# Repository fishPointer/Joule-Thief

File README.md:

# Joule Thief

## Overview
- **Purpose:** Exhibition project at Open Sauce July 18-20, 2025, Practice
- **Description:** High efficiency alkaline battery draining system with diagnostics and energy storage
- **Domain:** Precision energy harvesting & instrumentation

**Objectives:**
- Extract all usable electrical energy from used/"dead" Alkaline Cells (AA, AAA, etc.)
- Measure & Log energy extraction data from each cell & deliver analytics
- Efficiently convert and push energy extracted into a Li-Ion power bank

**Topology**
- **INA219** - Energy Metering
- **LTC3105** - Low Voltage Boost Converter
- **AD5280** - Digital Potentiometer, 200kΩ
- **DW01** - 18650 Single-cell BMS
- **TP4056** - Single-cell 18650 Charger
- **FS8205** - Dual-FET package for DW01
- **AO3400** - Low Voltage N-E-FET
- **1N5817** - Low Voltage Schottky Diode

**Status:** Complete. Exhibited. Working on Finalizing Documentation.

**Additional Documentation:** available on my Obsidian at [suneaterlabs.com](https://suneaterlabs.com).

**Why Joule Thief?**
This project was started as a New Year's Resolution to exhibit at Open Sauce 2025, and was finished 2 days prior to the event.
I have no commercial intent with this project. I don't believe that it is particularly novel, and a close look by anyone experienced with energy harvesting & power electronics should rightly reveal it as something akin to a useless machine.

I teach myself new skills by designing projects that require to develop the skills I want in order to complete them. I put a high level of effort into this project because I wanted to go through the process of designing a relatively performant embedded system without referencing anyone else's work. Just pick functionalities and features, set a spec, and then flip through datasheets until you find the right combination. Then put it all together and prove that it works. Design the schematic, route a board, write the firmware, etc. and then package it all up and provide thorough documentation on the whole thing.

I had never done any of that before and I have no professional experience working as an electronics engineer. I do have an EE degree and currently work in power system analysis for hyperscale datacenters, so this project is actually something like a microcosm of my day job. There is little overlap though, and I consider myself self-taught here. I learned a lot!

## System Description

### Joule Thief - Core Functionality

The Joule Thief is designed to fully deplete alkaline cells of any remaining energy, long after they will fail to turn on their devices. The core of this design is the LTC3105, which can handle input voltages as low as 250mV. A quick look at an alkaline cell's SOC-OCV curve will show that draining to 300mV is sufficient to say >99% of total energy has been drained.

The classic Joule Thief is a simple party trick involving a dead battery, a hand-wound toroid, and a BJT. It is essentially using the voltage spike from inductive kickback to PWM an LED back to life. My motivation for this project was to demonstrate that there is a considerable amount of energy left in alkaline cells when they are discarded, so I set out to build an overengineered energy harvester that could precisely quantify how much energy was actually left in a dead cell, and then store it into a lithium-based battery bank to further prove the point.

 In order to improve performance and maximize both energy throughput and conversion efficiency, there is an INA219 shunt meter on either side of the LTC3105 boost chip allowing for efficiency tracking during processing & live diagnostics. 
 Additionally, the LTC3105 includes an MPPC pin, which enables a variable resistance to throttle the inductor's switching in order to achieve a specified input voltage. With the addition of an AD5280-200kΩ digital potentiometer attached to the MPPC pin, it is possible to read in energy measurements from the INA219's into a microcontroller, and then adjust the setting of the LTC3105 accordingly. The result is a control loop that can maximize the energy extraction rate regardless of the target cell's health or state of charge. 
 
 This INA219+LTC3105+AD5280 system can be tuned for maximum efficiency or maximum average power extracted, but optimizing for energy throughput has far greater performance gains. Using a DC Electronic Load to produce a slow sweep of load resistance values across a fresh AA alkaline cell will result in no more than 400-500mW peak extraction rate, and chemical effects such as electrolyte gradient formation and ion depletion make this power output unstable and liable to rapidly decline. The dynamic approach explored in the Joule Thief is able to achieve 900-1100mW peak output power, and can reliably maintain 600-700mW extraction rate in the early life of a cell. Additionally, the MPPC schema prevents the cell's output capacity from being overwhelmed by the battery chemistry effects, and the cell will continuously output higher power than traditional Joule Thief circuits or static loads.

The Joule Thief Extraction Module is also designed to run in "headless" mode without an MCU. No diagnostics are available in this mode (obviously) and the board will be able to move the energy from a single AA cell into a single 18650 cell safely.

### Joule Chief - Core Functionality

The Joule Chief was designed to be a mainboard that allows for the consolidation of harvested energy from an arbitrary number of Joule Thief Extraction Modules collecting energy from different sources at different rates. The Joule Chief serves as both an aggregator and an abstraction layer for the energy harvested. 

The Joule Chief begins with a low-voltage schottky diode on the output of the extraction module to prevent backflow. After the energy is delivered to the mainboard's input bus, all the energy is stored in a 1F supercapacitor. The Joule Thief Extraction Modules are all set to boost whatever energy source they are targeting to 5V and charge the 1F supercap to 5V accordingly. 

Readings from the mainboard's INA219 allow the MCU to precisely track the voltage of the supercap as well as the power flowing into this buffer. The MCU is programmed to operate a schmitt trigger with thresholds at 2.5V and 5V, only enabling the 1F supercap's energy to pass through the mainboard's LTC3105 after 5V has been reached, and until 2.5V. This region of input voltage allows the boost chip to operate in a high-efficiency mode.

Once the energy has moved through the 1F supercap and through the LTC3105, it is stored in a second 1F supercap connected to the lithium cell charger. The cell charger is controlled by a second schmitt trigger running on the MCU as well. This schmitt trigger keeps the second 1F energy buffer between 4.5V and 5.0V, such that the buffer will always be an appropriate voltage for charging a lithium cell (3.0V to 4.3V).

The Joule Chief can handle an arbitrary number of extraction modules each working on arbitrarily weak or intermittent energy sources. This mainboard can effectively accumulate these energy sources and efficiently deposit this energy via intermittent pulses of energy into a rechargeable battery bank for later use while providing precise diagnostics at every stage of the harvesting process. The frequency of these charging pulses is dependent on the strength of the sources. Harvesting a sufficiently powerful source, such as a fresh AA cell, will allow the mainboard to achieve steady-state operation, and a continuous current flow into the 18650 becomes possible.

Both the Joule Thief and Joule Chief boards currently use a generic and inefficient BMS stack consisting of a DW01 for OC/OCD/SC protection, an FS8205 dual-FET package for breaking the circuit, and a TP4056 charging IC. This BMS is largely unnecessary given the low-power nature of this application, but was included for safety and peace of mind.

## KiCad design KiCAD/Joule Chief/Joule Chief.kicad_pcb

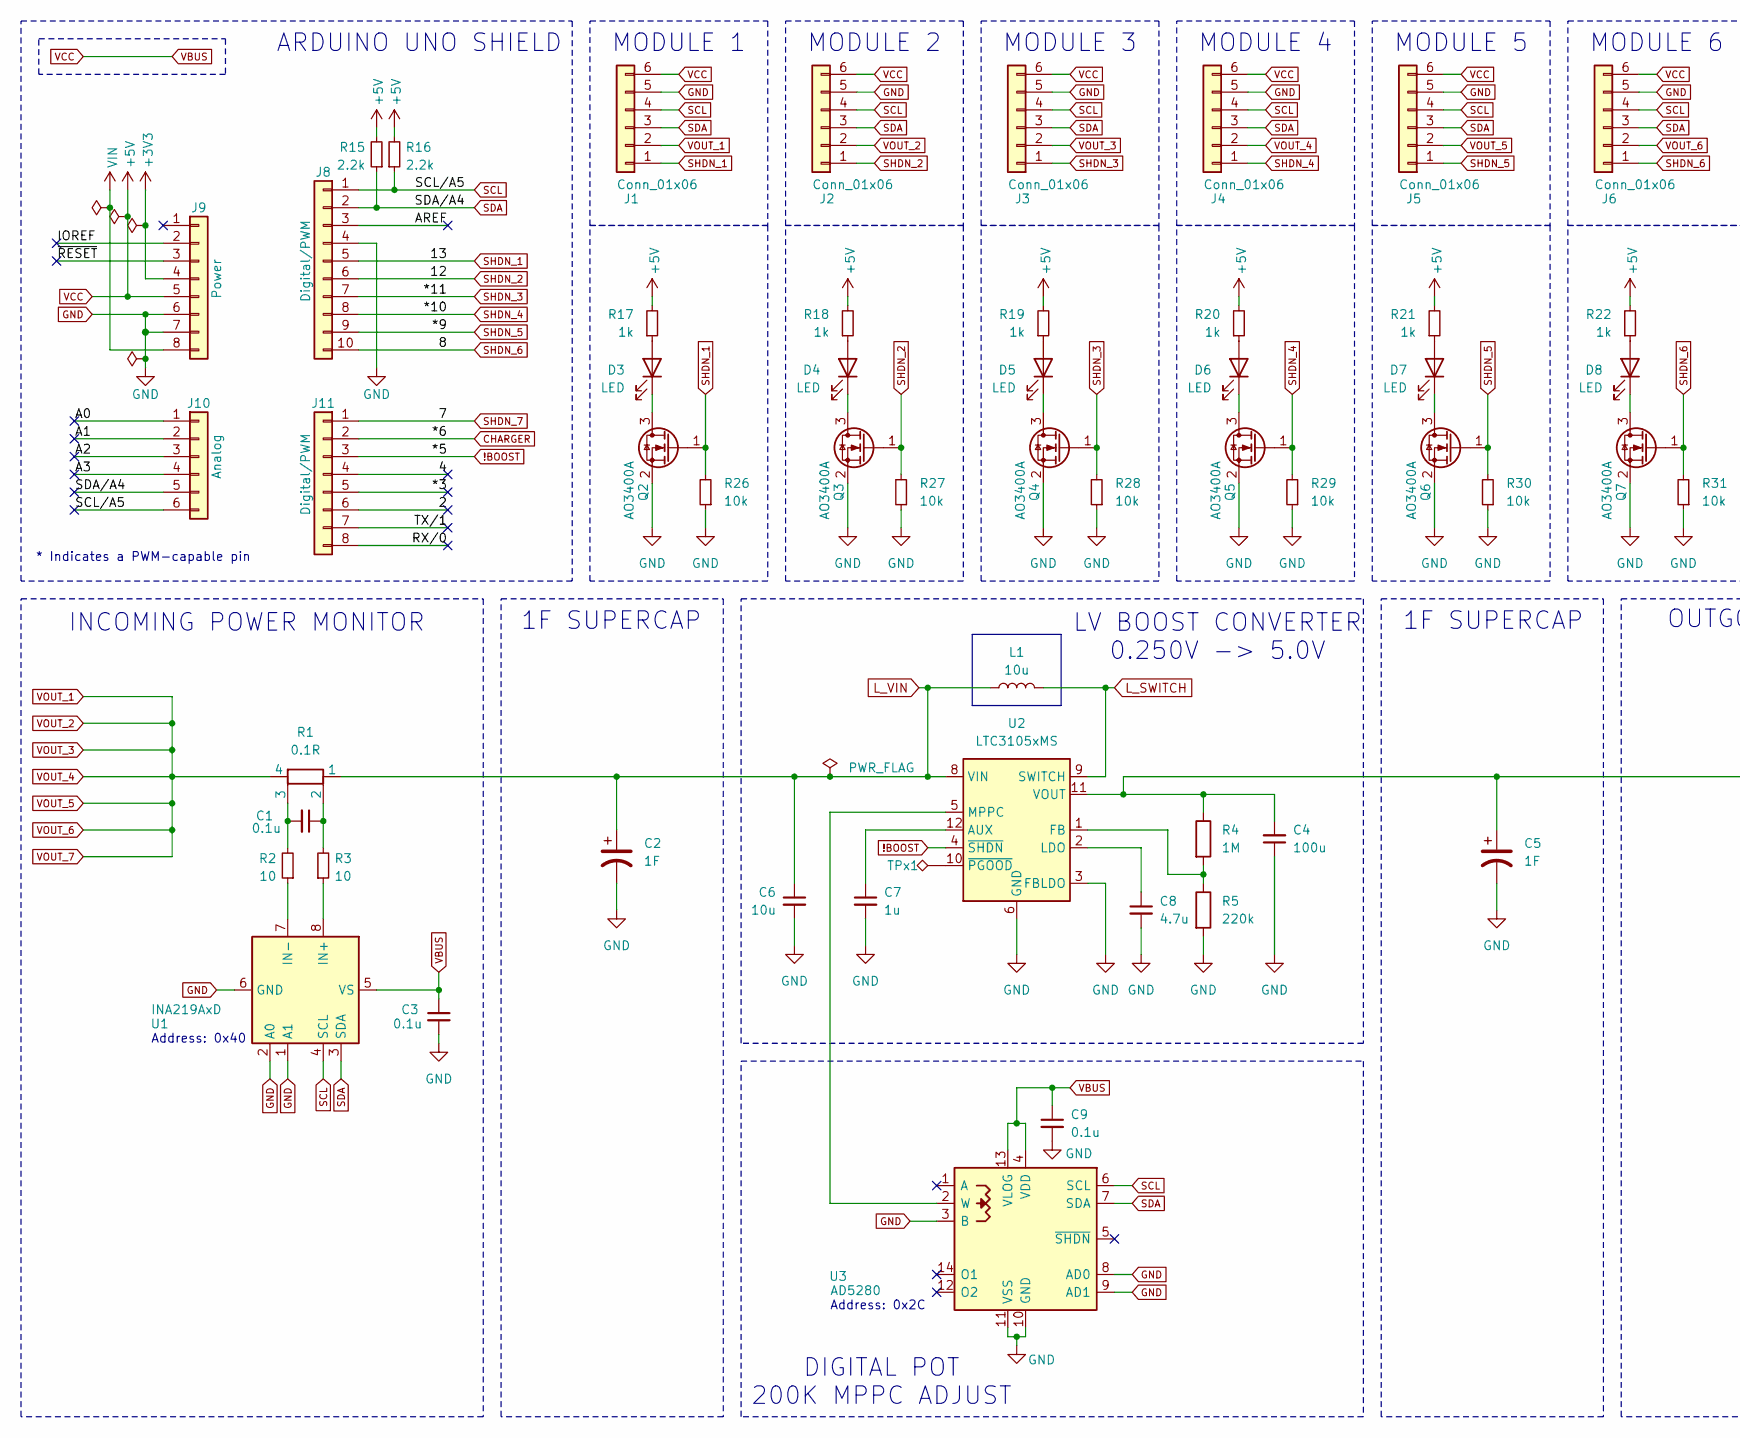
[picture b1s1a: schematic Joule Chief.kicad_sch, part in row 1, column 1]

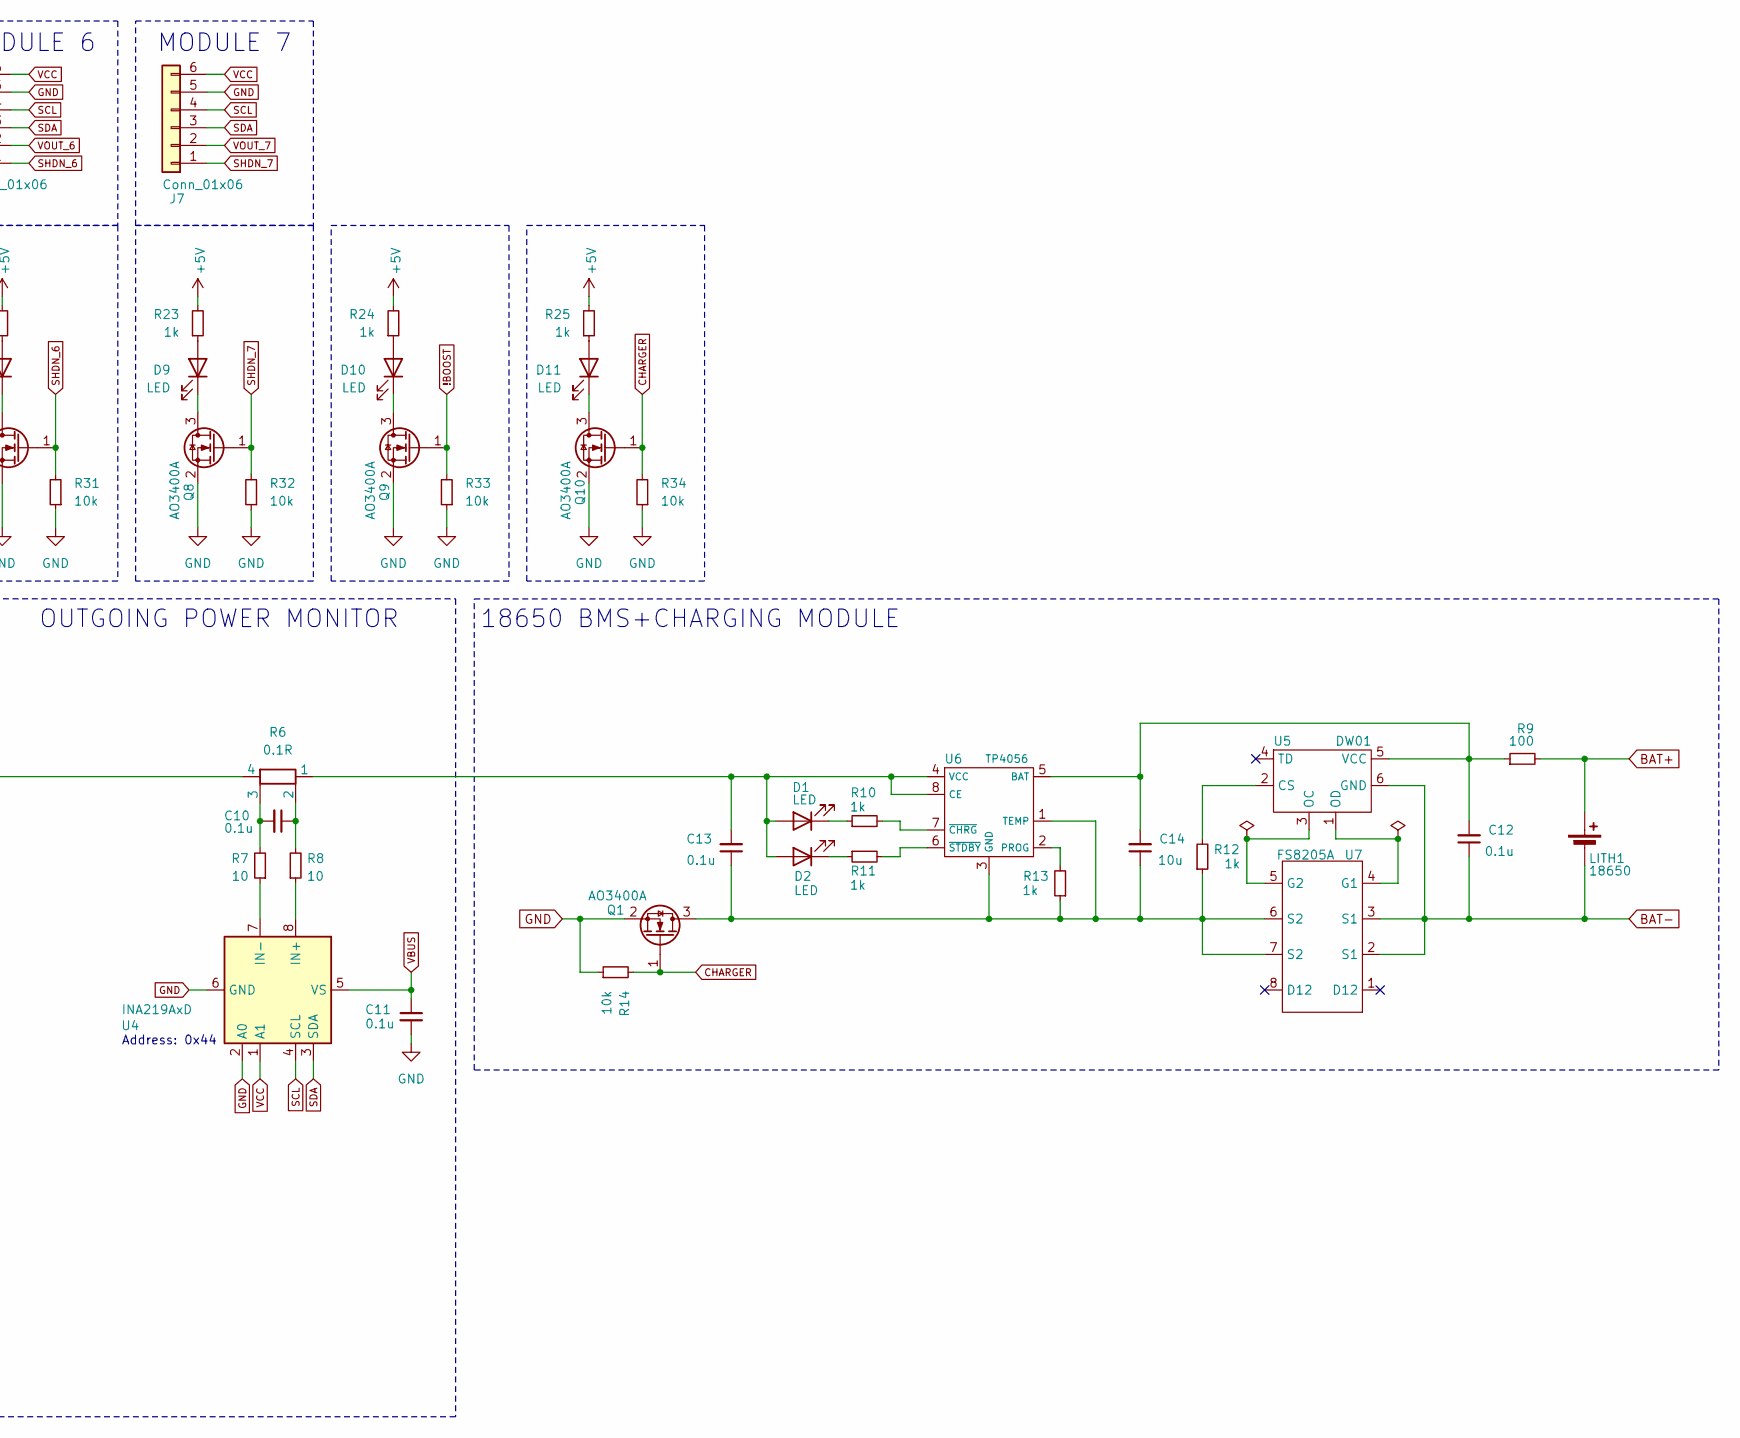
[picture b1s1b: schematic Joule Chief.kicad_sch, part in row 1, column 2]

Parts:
C1, C3, C9, C10, C11, C12, C13: 0.1u; C_0805_2012Metric_Pad1.18x1.45mm_HandSolder
C2, C5: 1F; 1F_Supercap
C4: 100u; CP_Radial_D5.0mm_P2.00mm
C6, C14: 10u; C_0805_2012Metric_Pad1.18x1.45mm_HandSolder
C7: 1u; C_0805_2012Metric_Pad1.18x1.45mm_HandSolder
C8: 4.7u; C_0805_2012Metric_Pad1.18x1.45mm_HandSolder
D1, D2, D3, D4, D5, D6, D7, D8, D9, D10, D11: LED; LED_0805_2012Metric_Pad1.15x1.40mm_HandSolder
J1, J2, J3, J4, J5, J6, J7: Conn_01x06; JST_PH_B6B-PH-K_1x06_P2.00mm_Vertical
J8: Digital/PWM; PinSocket_1x10_P2.54mm_Vertical
J9: Power; PinSocket_1x08_P2.54mm_Vertical
J10: Analog; PinSocket_1x06_P2.54mm_Vertical
J11: Digital/PWM; PinSocket_1x08_P2.54mm_Vertical
L1: 10u; Power_Inductor_101040
LITH1: 18650; 18650_Cell_Clip_V2
Q1, Q2, Q3, Q4, Q5, Q6, Q7, Q8, Q9, Q10: AO3400A; SOT-23
R1, R6: 0.1R; R_Shunt_2512_V2
R2, R3, R7, R8: 10; R_0805_2012Metric_Pad1.20x1.40mm_HandSolder
R4: 1M; R_0805_2012Metric_Pad1.20x1.40mm_HandSolder
R5: 220k; R_0805_2012Metric_Pad1.20x1.40mm_HandSolder
R9: 100; R_0805_2012Metric_Pad1.20x1.40mm_HandSolder
R10, R11, R12, R13, R17, R18, R19, R20, R21, R22, R23, R24, R25: 1k; R_0805_2012Metric_Pad1.20x1.40mm_HandSolder
R14, R26, R27, R28, R29, R30, R31, R32, R33, R34: 10k; R_0805_2012Metric_Pad1.20x1.40mm_HandSolder
R15, R16: 2.2k; R_0805_2012Metric_Pad1.20x1.40mm_HandSolder
TPx1: TestPoint_Alt; TestPoint_THTPad_1.0x1.0mm_Drill0.5mm
U1, U4: INA219AxD; SOIC-8_3.9x4.9mm_P1.27mm
U2: LTC3105xMS; MSOP-12_3x4.039mm_P0.65mm
U3: AD5280; TSSOP-14_4.4x5mm_P0.65mm
U5: DW01; SOT-23-6_Handsoldering
U6: TP4056; SOIC-8-1EP_3.9x4.9mm_P1.27mm_EP2.29x3mm
U7: FS8205A; FS8205A_Wide

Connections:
!BOOST: J11.3, Q9.1 (G), R33.2, U2.4 (~SHDN)
+3V3: J9.4
/2: J11.6
/4: J11.4
/*3: J11.5
/A0: J10.1
/A1: J10.2
/A2: J10.3
/A3: J10.4
/AREF: J8.3
/IOREF: J9.2
/RX/0: J11.8
/TX/1: J11.7
/~RESET: J9.3
BAT+: LITH1.1 (+), R9.2
BAT-: C12.1, LITH1.2 (-), U5.6 (GND), U7.2 (S1), U7.3 (S1)
CHARGER: J11.2, Q1.1 (G), Q10.1 (G), R14.2, R34.2
GND: C2.2, C3.2, C4.1, C5.2, C6.2, C7.2, C8.2, C9.2, C11.2, J1.5, J2.5, J3.5, J4.5, J5.5, J6.5, J7.5, J8.4, J9.6, J9.7, Q1.2 (S), Q2.2 (S), Q3.2 (S), Q4.2 (S), Q5.2 (S), Q6.2 (S), Q7.2 (S), Q8.2 (S), Q9.2 (S), Q10.2 (S), R5.2, R14.1, R26.1, R27.1, R28.1, R29.1, R30.1, R31.1, R32.1, R33.1, R34.1, U1.1 (A1), U1.2 (A0), U1.6 (GND), U2.3 (FBLDO), U2.6 (GND), U2.7 (GND), U3.3 (B), U3.8 (AD0), U3.9 (AD1), U3.10 (GND), U3.11 (VSS), U4.2 (A0), U4.6 (GND)
L_SWITCH: L1.2, U2.9 (SWITCH)
L_VIN: C2.1, C6.1, L1.1, R1.1, U2.8 (VIN)
unnamed: C1.1, R1.2, R3.2
unnamed: C1.2, R1.3, R2.2
unnamed: C10.1, R6.2, R8.2
unnamed: C10.2, R6.3, R7.2
unnamed: C13.2, D1.2 (A), D2.2 (A), R6.1, U6.4 (VCC), U6.8 (CE)
unnamed: D1.1 (K), R10.1
unnamed: D2.1 (K), R11.1
unnamed: D3.2 (A), R17.1
unnamed: D3.1 (K), Q2.3 (D)
unnamed: D4.2 (A), R18.1
unnamed: D4.1 (K), Q3.3 (D)
unnamed: D5.2 (A), R19.1
unnamed: D5.1 (K), Q4.3 (D)
unnamed: D6.2 (A), R20.1
unnamed: D6.1 (K), Q5.3 (D)
unnamed: D7.2 (A), R21.1
unnamed: D7.1 (K), Q6.3 (D)
unnamed: D8.2 (A), R22.1
unnamed: D8.1 (K), Q7.3 (D)
unnamed: D9.2 (A), R23.1
unnamed: D9.1 (K), Q8.3 (D)
unnamed: D10.2 (A), R24.1
unnamed: D10.1 (K), Q9.3 (D)
unnamed: D11.2 (A), R25.1
unnamed: D11.1 (K), Q10.3 (D)
unnamed: C13.1, C14.1, Q1.3 (D), R12.1, R13.1, U6.1 (TEMP), U6.3 (GND), U7.6 (S2), U7.7 (S2)
unnamed: R3.1, U1.8 (IN+)
unnamed: R2.1, U1.7 (IN-)
unnamed: C7.1, U2.12 (AUX)
unnamed: R4.2, R5.1, U2.1 (FB)
unnamed: C8.1, U2.2 (LDO)
unnamed: U2.5 (MPPC), U3.2 (W)
unnamed: C4.2, C5.1, R4.1, R6.4, U2.11 (VOUT)
unnamed: TPx1.1, U2.10 (~PGOOD)
unnamed: R8.1, U4.8 (IN+)
unnamed: R7.1, U4.7 (IN-)
unnamed: R12.2, U5.2 (CS)
unnamed: U5.3 (OC), U7.5 (G2)
unnamed: U5.1 (OD), U7.4 (G1)
unnamed: C12.2, C14.2, R9.1, U5.5 (VCC), U6.5 (BAT)
unnamed: R13.2, U6.2 (PROG)
unnamed: R10.2, U6.7 (~CHRG)
unnamed: R11.2, U6.6 (~STDBY)
SCL: J1.4, J2.4, J3.4, J4.4, J5.4, J6.4, J7.4, J8.1, J10.6, R16.1, U1.4 (SCL), U3.6 (SCL), U4.4 (SCL)
SDA: J1.3, J2.3, J3.3, J4.3, J5.3, J6.3, J7.3, J8.2, J10.5, R15.1, U1.3 (SDA), U3.7 (SDA), U4.3 (SDA)
SHDN_1: J1.1, J8.5, Q2.1 (G), R26.2
SHDN_2: J2.1, J8.6, Q3.1 (G), R27.2
SHDN_3: J3.1, J8.7, Q4.1 (G), R28.2
SHDN_4: J4.1, J8.8, Q5.1 (G), R29.2
SHDN_5: J5.1, J8.9, Q6.1 (G), R30.2
SHDN_6: J6.1, J8.10, Q7.1 (G), R31.2
SHDN_7: J7.1, J11.1, Q8.1 (G), R32.2
VBUS: C3.1, C9.1, C11.1, J1.6, J2.6, J3.6, J4.6, J5.6, J6.6, J7.6, J9.5, R15.2, R16.2, R17.2, R18.2, R19.2, R20.2, R21.2, R22.2, R23.2, R24.2, R25.2, U1.5 (VS), U3.4 (VDD), U3.13 (VLOG), U4.1 (A1), U4.5 (VS)
VIN: J9.8
VOUT_1: J1.2, J2.2, J3.2, J4.2, J5.2, J6.2, J7.2, R1.4

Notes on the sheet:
INCOMING POWER MONITOR
Address: 0x40
MODULE 3
LV BOOST CONVERTER 0.250V -> 5.0V
Address: 0x2C
OUTGOING POWER MONITOR
1F SUPERCAP
18650 BMS+CHARGING MODULE
MODULE 4
ARDUINO UNO SHIELD
Address: 0x44
MODULE 1
DIGITAL POT 200K MPPC ADJUST
MODULE 5
MODULE 6
* Indicates a PWM-capable pin
MODULE 7
MODULE 2

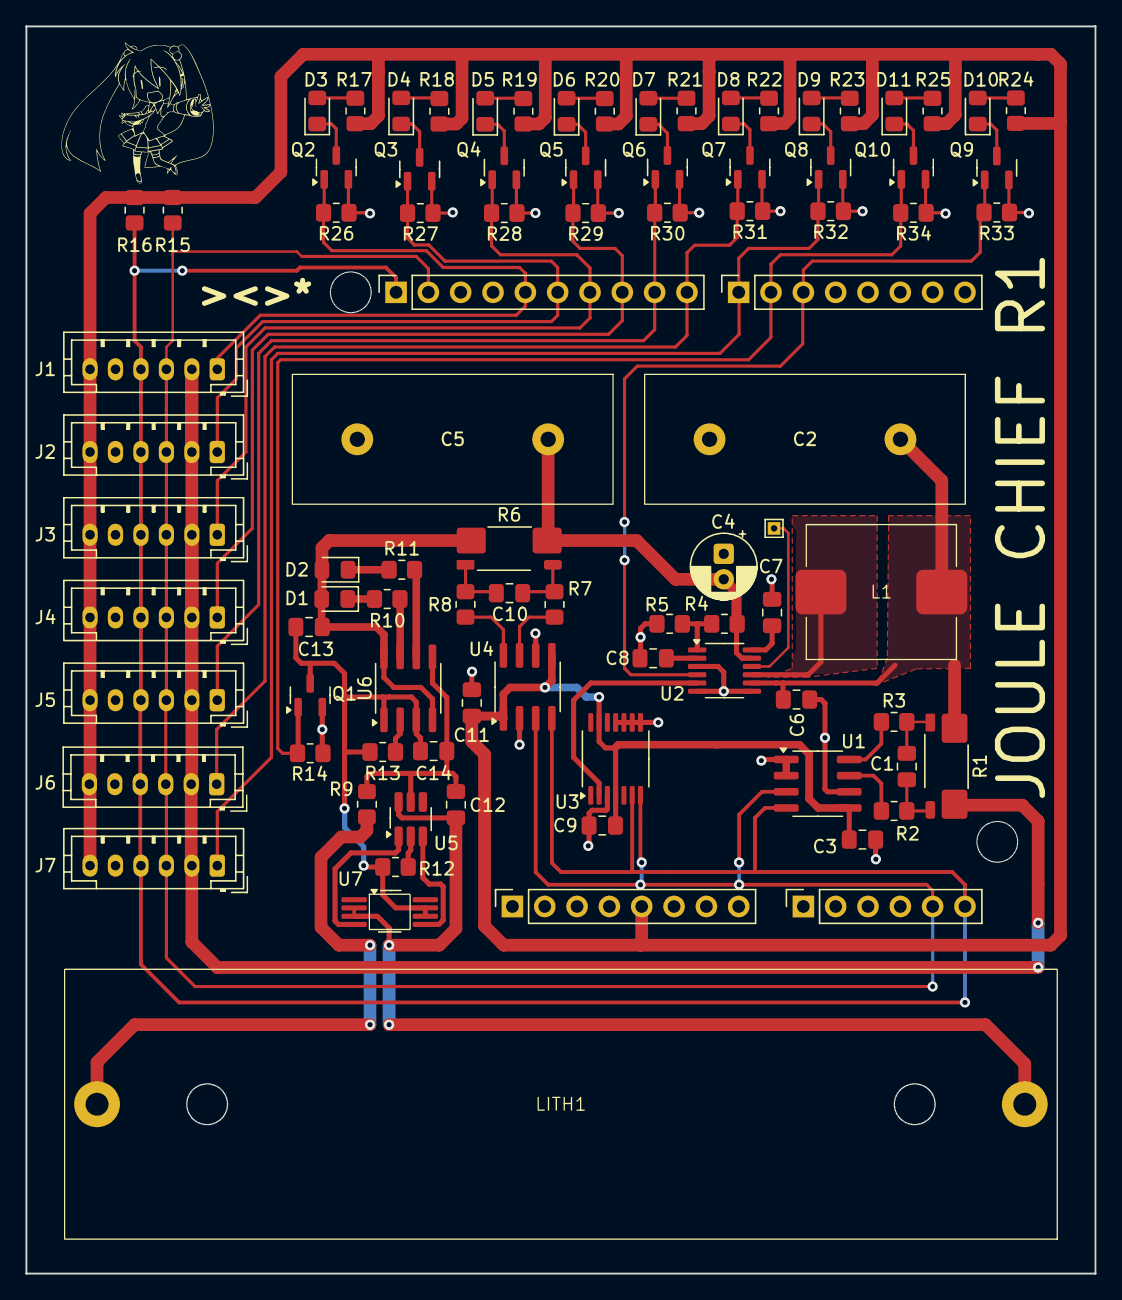
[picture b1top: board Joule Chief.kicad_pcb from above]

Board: 2 copper layers, 84.0 x 98.0 mm, 92 parts (0 on the bottom side), 61 nets.

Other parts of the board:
MH1, MH4: MountingHole_3.2mm

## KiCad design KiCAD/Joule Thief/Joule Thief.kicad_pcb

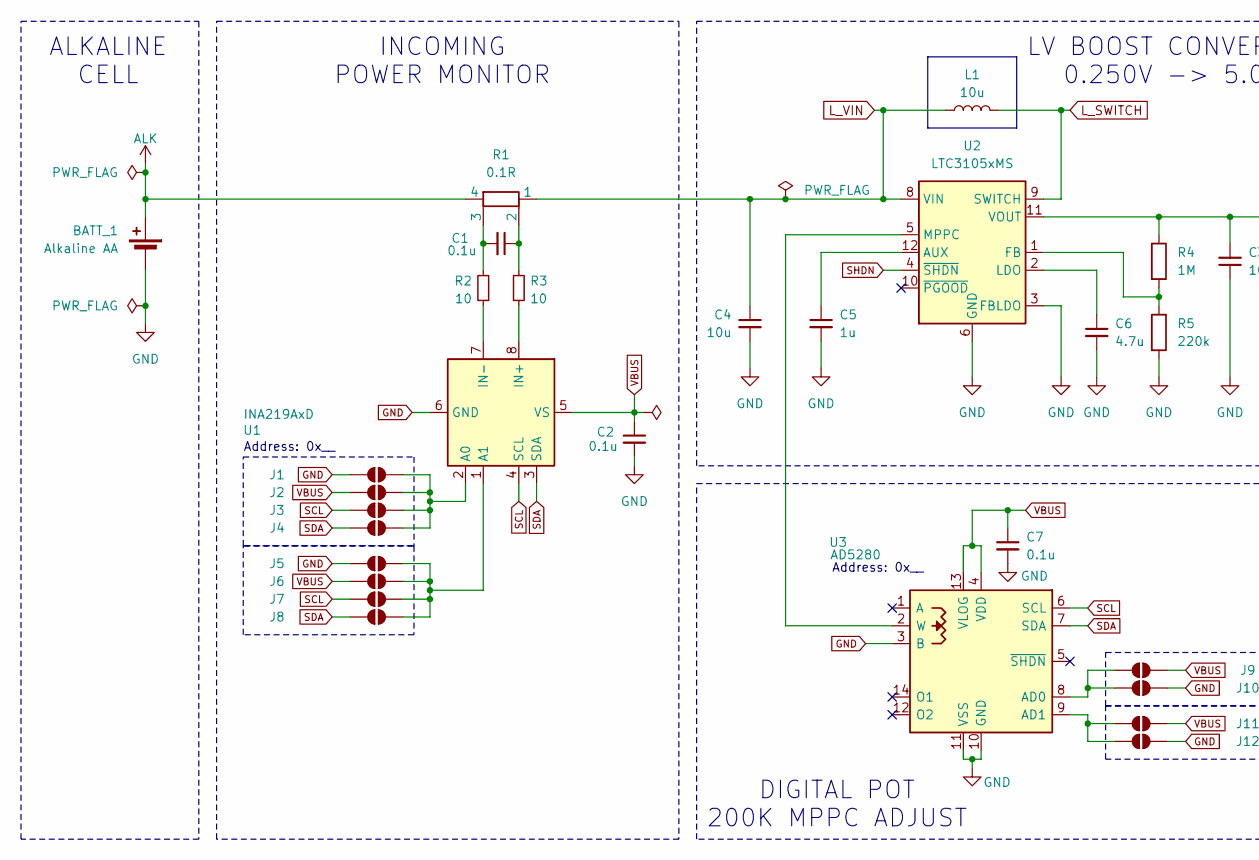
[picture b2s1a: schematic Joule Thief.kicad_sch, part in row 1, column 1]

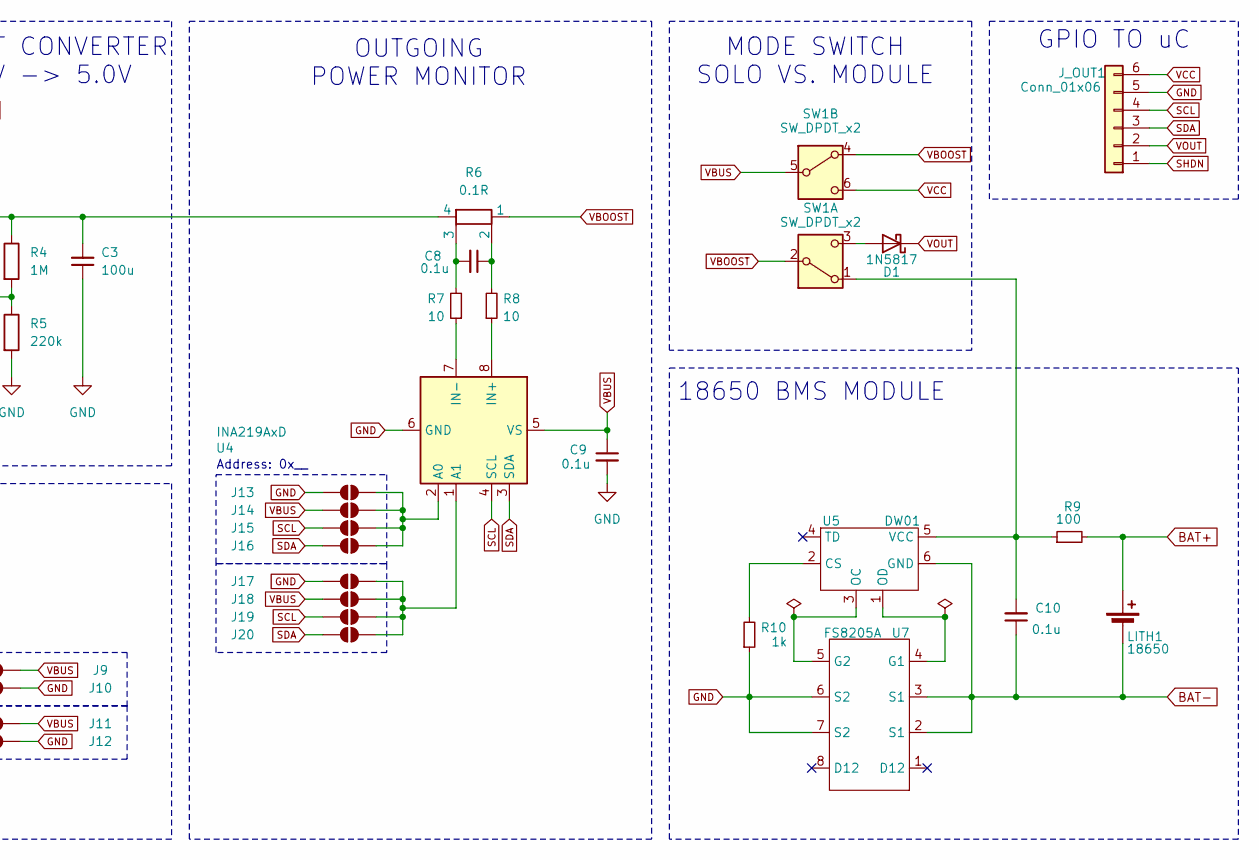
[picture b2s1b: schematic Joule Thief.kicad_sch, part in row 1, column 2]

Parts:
BATT_1: Alkaline AA; AA_Cell_Clip_V2
C1, C2, C7, C8, C9, C10: 0.1u; C_0805_2012Metric_Pad1.18x1.45mm_HandSolder
C3: 100u; CP_Radial_D5.0mm_P2.00mm
C4: 10u; C_0805_2012Metric_Pad1.18x1.45mm_HandSolder
C5: 1u; C_0805_2012Metric_Pad1.18x1.45mm_HandSolder
C6: 4.7u; C_0805_2012Metric_Pad1.18x1.45mm_HandSolder
D1: 1N5817; D_DO-41_SOD81_P10.16mm_Horizontal
J1, J2, J3, J4, J5, J6, J7, J8, J9, J10, J11, J12, J13, J14, J15, J16, J17, J18, J19, J20: SolderJumper_2_Open; SolderJumper-2_P1.3mm_Open_RoundedPad1.0x1.5mm
J_OUT1: Conn_01x06; JST_PH_B6B-PH-K_1x06_P2.00mm_Vertical
L1: 10u; Power_Inductor_101040
LITH1: 18650; 18650_Cell_Clip_V2
R1, R6: 0.1R; R_Shunt_2512_V2
R2, R3, R7, R8: 10; R_0805_2012Metric_Pad1.20x1.40mm_HandSolder
R4: 1M; R_0805_2012Metric_Pad1.20x1.40mm_HandSolder
R5: 220k; R_0805_2012Metric_Pad1.20x1.40mm_HandSolder
R9: 100; R_0805_2012Metric_Pad1.20x1.40mm_HandSolder
R10: 1k; R_0805_2012Metric_Pad1.20x1.40mm_HandSolder
SW1: SW_DPDT_x2; SS22F25_DPDT_Straight_V2
U1, U4: INA219AxD; SOIC-8_3.9x4.9mm_P1.27mm
U2: LTC3105xMS; MSOP-12_3x4.039mm_P0.65mm
U3: AD5280; TSSOP-14_4.4x5mm_P0.65mm
U5: DW01; SOT-23-6_Handsoldering
U7: FS8205A; FS8205A_Wide

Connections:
ALK: BATT_1.1 (+), R1.4
BAT+: LITH1.1 (+), R9.2
BAT-: C10.1, LITH1.2 (-), U5.6 (GND), U7.2 (S1), U7.3 (S1)
GND: BATT_1.2 (-), C2.2, C3.1, C4.2, C5.2, C6.2, C7.2, C9.2, J1.2 (B), J5.2 (B), J10.2 (B), J12.2 (B), J13.2 (B), J17.2 (B), J_OUT1.5, R5.2, R10.1, U1.6 (GND), U2.3 (FBLDO), U2.6 (GND), U2.7 (GND), U3.3 (B), U3.10 (GND), U3.11 (VSS), U4.6 (GND), U7.6 (S2), U7.7 (S2)
L_SWITCH: L1.2, U2.9 (SWITCH)
L_VIN: C4.1, L1.1, R1.1, U2.8 (VIN)
unnamed: C1.1, R1.2, R3.2
unnamed: C1.2, R1.3, R2.2
unnamed: C8.1, R6.2, R8.2
unnamed: C8.2, R6.3, R7.2
unnamed: D1.2 (A), SW1.3 (C)
unnamed: J1.1 (A), J2.1 (A), J3.1 (A), J4.1 (A), U1.2 (A0)
unnamed: J5.1 (A), J6.1 (A), J7.1 (A), J8.1 (A), U1.1 (A1)
unnamed: J9.1 (A), J10.1 (A), U3.8 (AD0)
unnamed: J11.1 (A), J12.1 (A), U3.9 (AD1)
unnamed: J13.1 (A), J14.1 (A), J15.1 (A), J16.1 (A), U4.2 (A0)
unnamed: J17.1 (A), J18.1 (A), J19.1 (A), J20.1 (A), U4.1 (A1)
unnamed: C10.2, R9.1, SW1.1 (A), U5.5 (VCC)
unnamed: R3.1, U1.8 (IN+)
unnamed: R2.1, U1.7 (IN-)
unnamed: C5.1, U2.12 (AUX)
unnamed: R4.2, R5.1, U2.1 (FB)
unnamed: C6.1, U2.2 (LDO)
unnamed: U2.5 (MPPC), U3.2 (W)
unnamed: C3.2, R4.1, R6.4, U2.11 (VOUT)
unnamed: R8.1, U4.8 (IN+)
unnamed: R7.1, U4.7 (IN-)
unnamed: R10.2, U5.2 (CS)
unnamed: U5.3 (OC), U7.5 (G2)
unnamed: U5.1 (OD), U7.4 (G1)
SCL: J3.2 (B), J7.2 (B), J15.2 (B), J19.2 (B), J_OUT1.4, U1.4 (SCL), U3.6 (SCL), U4.4 (SCL)
SDA: J4.2 (B), J8.2 (B), J16.2 (B), J20.2 (B), J_OUT1.3, U1.3 (SDA), U3.7 (SDA), U4.3 (SDA)
SHDN: J_OUT1.1, U2.4 (~SHDN)
VBOOST: R6.1, SW1.2 (B), SW1.4 (A)
VBUS: C2.1, C7.1, C9.1, J2.2 (B), J6.2 (B), J9.2 (B), J11.2 (B), J14.2 (B), J18.2 (B), SW1.5 (B), U1.5 (VS), U3.4 (VDD), U3.13 (VLOG), U4.5 (VS)
VCC: J_OUT1.6, SW1.6 (C)
VOUT: D1.1 (K), J_OUT1.2

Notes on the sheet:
Address: 0x__
DIGITAL POT 200K MPPC ADJUST
INCOMING POWER MONITOR
ALKALINE CELL
Address: 0x__
OUTGOING POWER MONITOR
18650 BMS MODULE
MODE SWITCH SOLO VS. MODULE
GPIO TO uC
LV BOOST CONVERTER 0.250V -> 5.0V

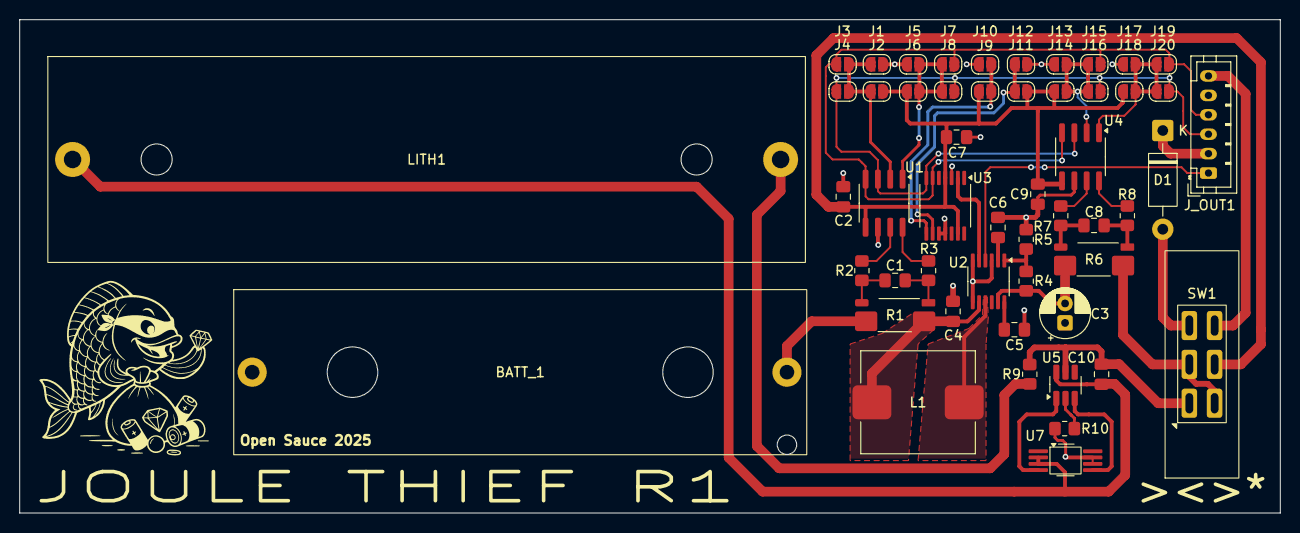
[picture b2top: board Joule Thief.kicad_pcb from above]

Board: 2 copper layers, 129.8 x 50.8 mm, 52 parts (0 on the bottom side), 37 nets.

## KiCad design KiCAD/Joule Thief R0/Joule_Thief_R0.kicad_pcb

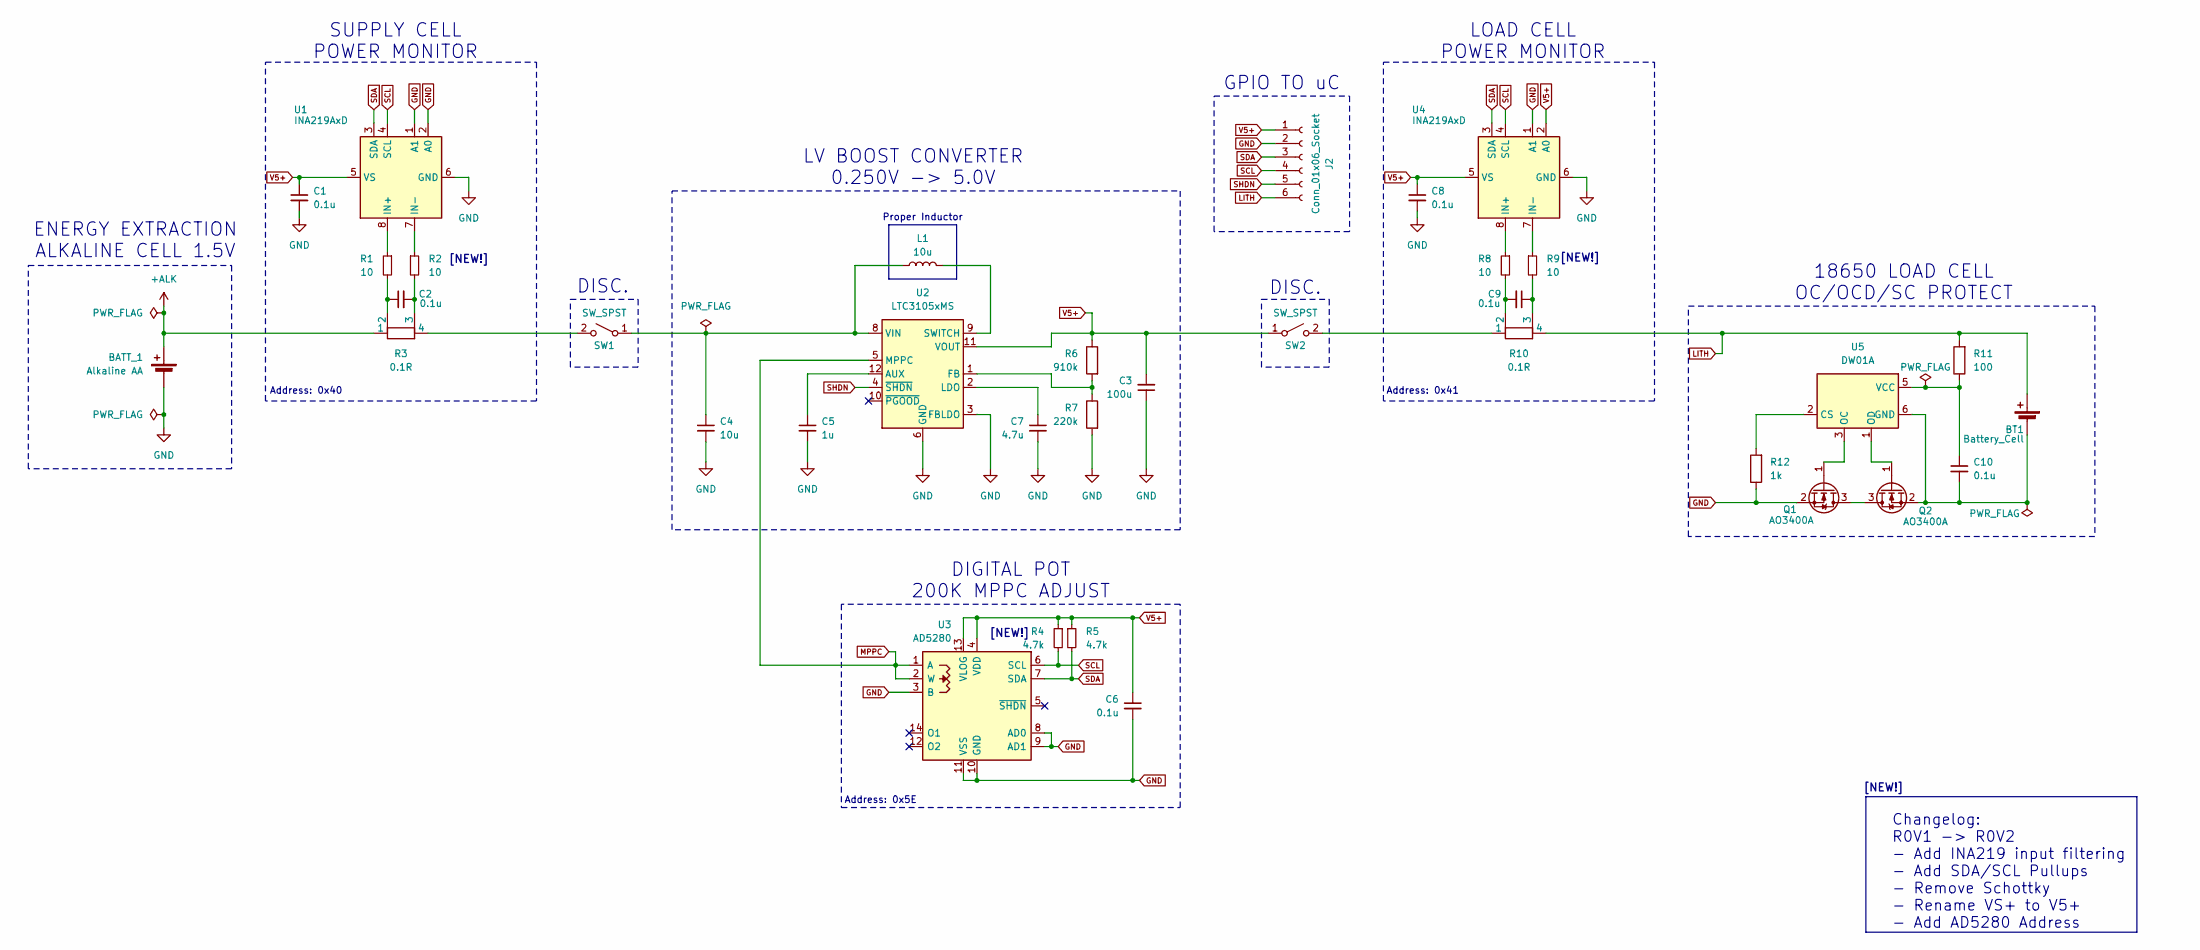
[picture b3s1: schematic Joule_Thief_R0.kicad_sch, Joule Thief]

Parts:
BATT_1: Alkaline AA; AA_Cell_Clip
BT1: Battery_Cell; 18650_Cell_Clip
C1, C2, C6, C8, C9, C10: 0.1u; C_0805_2012Metric_Pad1.18x1.45mm_HandSolder
C3: 100u; C_0805_2012Metric_Pad1.18x1.45mm_HandSolder
C4: 10u; C_0805_2012Metric_Pad1.18x1.45mm_HandSolder
C5: 1u; C_0805_2012Metric_Pad1.18x1.45mm_HandSolder
C7: 4.7u; C_0805_2012Metric_Pad1.18x1.45mm_HandSolder
J2: Conn_01x06_Socket; PinSocket_1x06_P2.54mm_Vertical
L1: 10u; Power_Inductor_101040
Q1, Q2: AO3400A; SOT-23
R1, R2, R8, R9: 10; R_0805_2012Metric_Pad1.20x1.40mm_HandSolder
R3, R10: 0.1R; R_Shunt_Vishay_WSK2512_6332Metric_T1.19mm
R4, R5: 4.7k; R_0805_2012Metric_Pad1.20x1.40mm_HandSolder
R6: 910k; R_0805_2012Metric_Pad1.20x1.40mm_HandSolder
R7: 220k; R_0805_2012Metric_Pad1.20x1.40mm_HandSolder
R11: 100; R_0805_2012Metric_Pad1.20x1.40mm_HandSolder
R12: 1k; R_0805_2012Metric_Pad1.20x1.40mm_HandSolder
SW1, SW2: SW_SPST; SMD_DPST_Switch
U1, U4: INA219AxD; SOIC-8_3.9x4.9mm_P1.27mm
U2: LTC3105xMS; MSOP-12_3x4.039mm_P0.65mm
U3: AD5280; TSSOP-14_4.4x5mm_P0.65mm
U5: DW01A; SOT-23-6

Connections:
+ALK: BATT_1.1 (+), R3.1
GND: BATT_1.2 (-), C1.2, C3.1, C4.2, C5.2, C6.2, C7.2, C8.2, J2.2, Q1.2 (S), R7.2, R12.1, U1.1 (A1), U1.2 (A0), U1.6 (GND), U2.3 (FBLDO), U2.6 (GND), U2.7 (GND), U3.3 (B), U3.8 (AD0), U3.9 (AD1), U3.10 (GND), U3.11 (VSS), U4.1 (A1), U4.6 (GND)
LITH: BT1.1 (+), J2.6, R10.4, R11.2
MPPC: U2.5 (MPPC), U3.1 (A), U3.2 (W)
unnamed: BT1.2 (-), C10.2, Q2.2 (S), U5.6 (GND)
unnamed: C2.1, R1.2, R3.2
unnamed: C2.2, R2.2, R3.3
unnamed: C9.1, R9.2, R10.3
unnamed: C9.2, R8.2, R10.2
unnamed: Q1.3 (D), Q2.3 (D)
unnamed: Q1.1 (G), U5.3 (OC)
unnamed: Q2.1 (G), U5.1 (OD)
unnamed: C4.1, L1.1, SW1.1 (A), U2.8 (VIN)
unnamed: R3.4, SW1.2 (B)
unnamed: R10.1, SW2.2 (B)
unnamed: R1.1, U1.8 (IN+)
unnamed: R2.1, U1.7 (IN-)
unnamed: C5.1, U2.12 (AUX)
unnamed: R6.2, R7.1, U2.1 (FB)
unnamed: C7.1, U2.2 (LDO)
unnamed: L1.2, U2.9 (SWITCH)
unnamed: R8.1, U4.8 (IN+)
unnamed: R9.1, U4.7 (IN-)
unnamed: R12.2, U5.2 (CS)
unnamed: C10.1, R11.1, U5.5 (VCC)
SCL: J2.4, R4.2, U1.4 (SCL), U3.6 (SCL), U4.4 (SCL)
SDA: J2.3, R5.2, U1.3 (SDA), U3.7 (SDA), U4.3 (SDA)
SHDN: J2.5, U2.4 (~SHDN)
V5+: C1.1, C3.2, C6.1, C8.1, J2.1, R4.1, R5.1, R6.1, SW2.1 (A), U1.5 (VS), U2.11 (VOUT), U3.4 (VDD), U3.13 (VLOG), U4.2 (A0), U4.5 (VS)

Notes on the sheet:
Address: 0x41
DIGITAL POT 200K MPPC ADJUST
[NEW!]
SUPPLY CELL POWER MONITOR
ENERGY EXTRACTION ALKALINE CELL 1.5V
Address: 0x5E
DISC.
LOAD CELL POWER MONITOR
GPIO TO uC
18650 LOAD CELL OC/OCD/SC PROTECT
Address: 0x40
Changelog: R0V1 -> R0V2 - Add INA219 input filtering - Add SDA/SCL Pullups - Remove Schottky - Rename VS+ to V5+ - Add AD5280 Address
Proper Inductor
LV BOOST CONVERTER 0.250V -> 5.0V

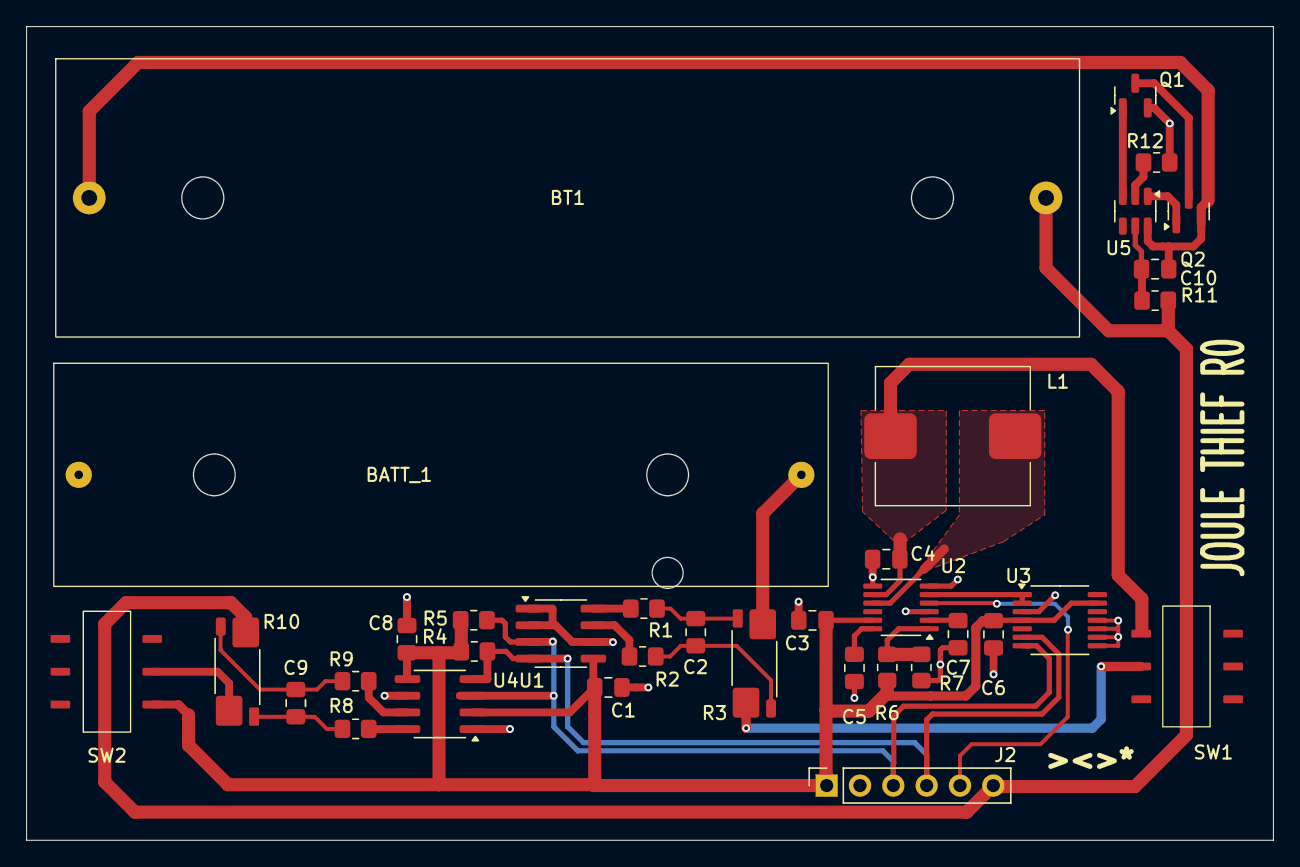
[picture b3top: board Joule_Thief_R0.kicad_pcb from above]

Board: 2 copper layers, 95.0 x 62.0 mm, 35 parts (0 on the bottom side), 29 nets.
